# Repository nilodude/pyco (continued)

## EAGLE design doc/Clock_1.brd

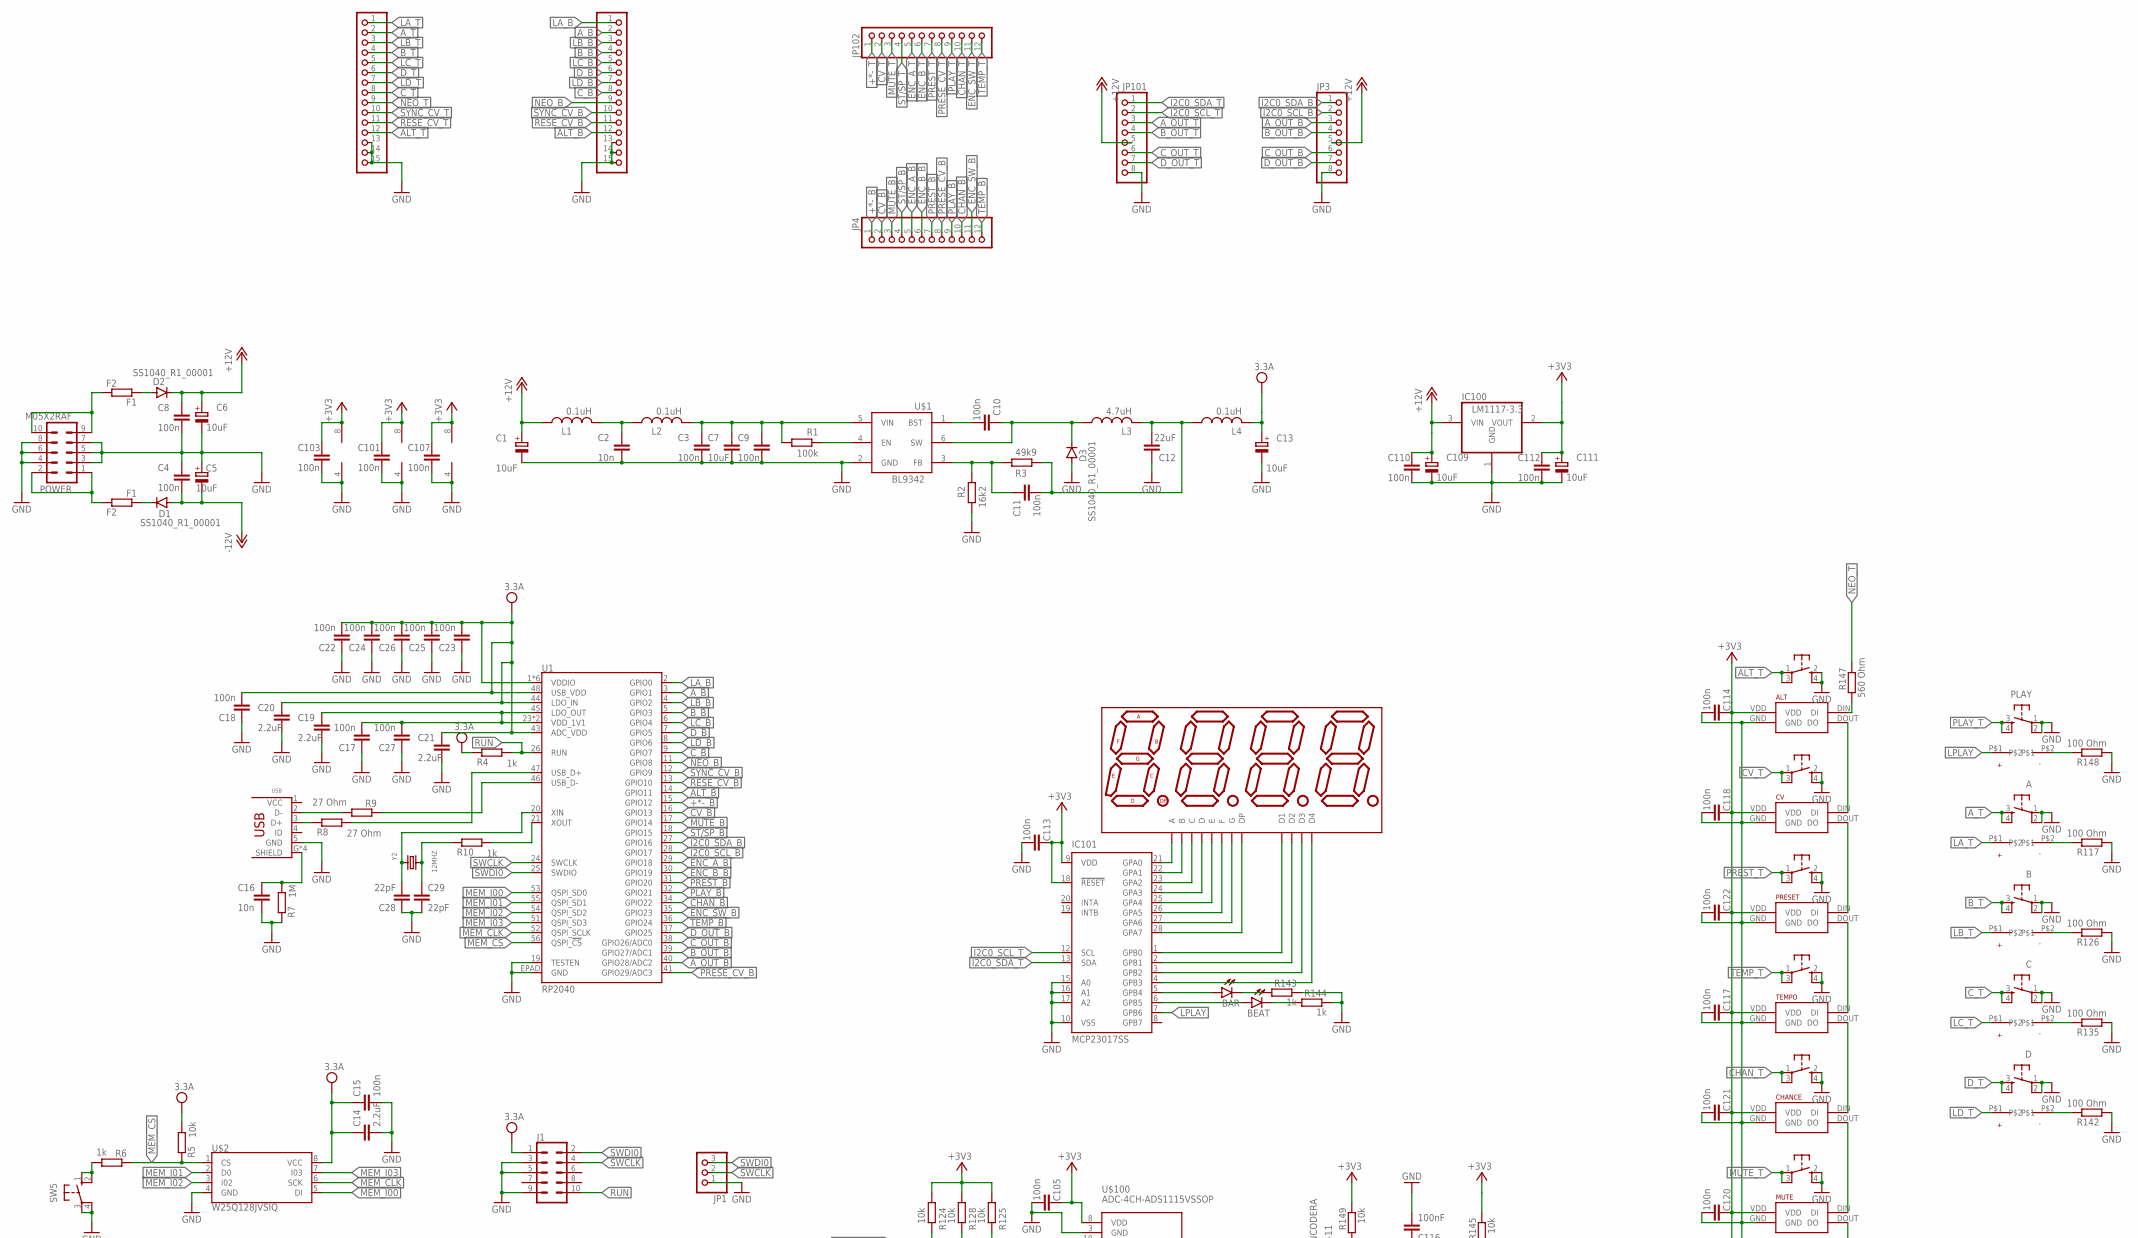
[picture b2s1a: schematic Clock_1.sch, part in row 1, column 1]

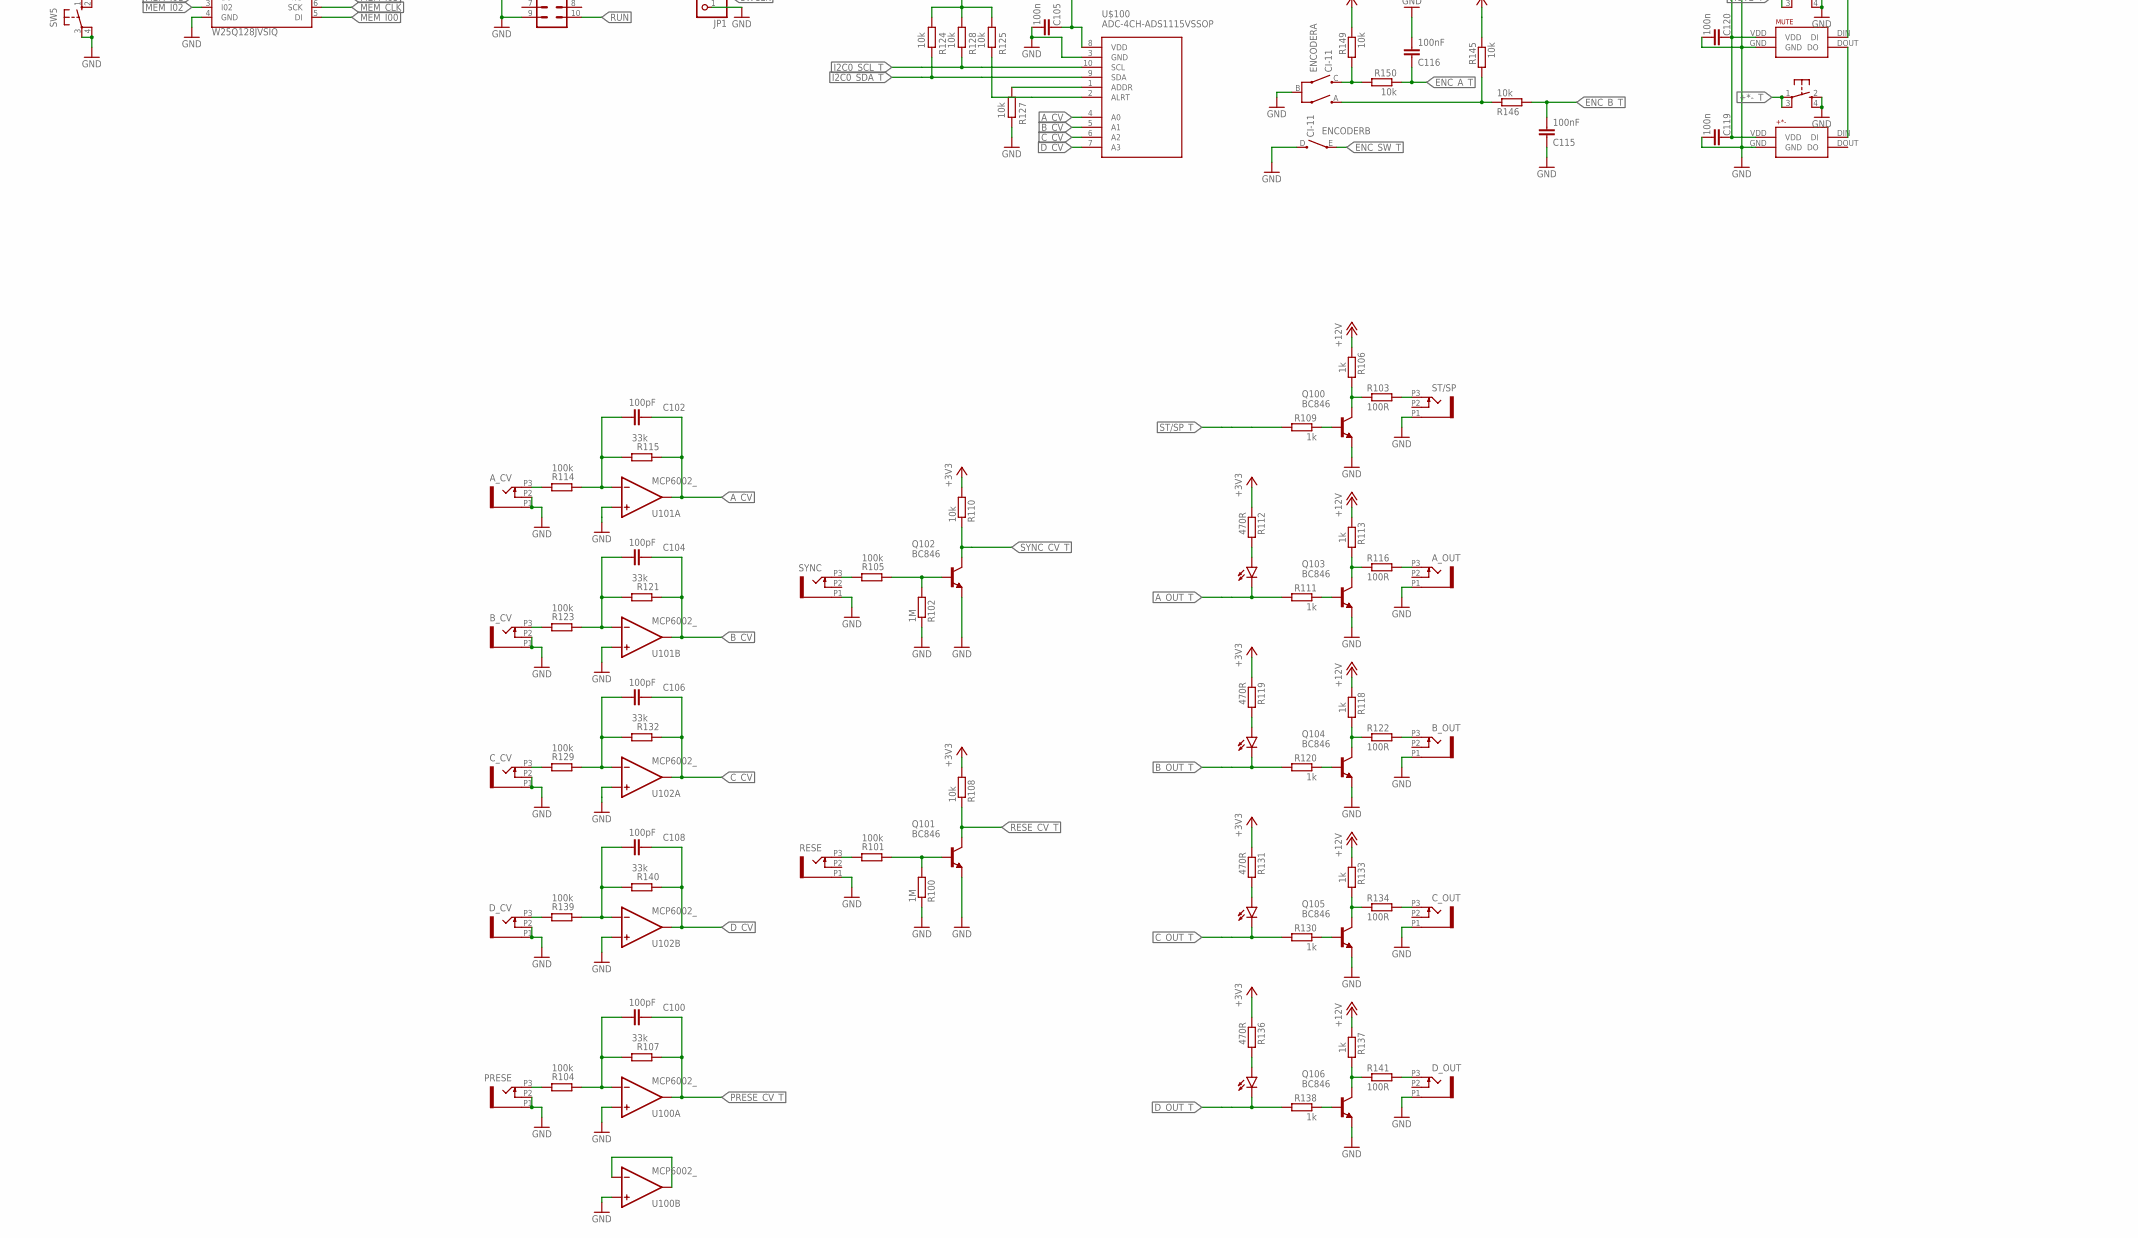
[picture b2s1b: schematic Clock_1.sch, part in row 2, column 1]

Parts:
+*-: BUTTON_NEOPIXELBUTTON_PIXEL_ç; BUTTON_PIXEL_ç
A: DTS-6_LEDTME; TMEBUTTON
ALT: BUTTON_NEOPIXELBUTTON_PIXEL_ç; BUTTON_PIXEL_ç
A_CV: OG-PJ301_PJ301_THONKICONNNOHOLER; NOHOLER_GND_SHORT_PADMINI_GND
A_OUT: OG-PJ301_PJ301_THONKICONNNOHOLER; NOHOLER_GND_SHORT_PADMINI_GND
B: DTS-6_LEDTME; TMEBUTTON
BAR: 2 MM LED; LED3MM
BEAT: 2 MM LED; LED3MM
B_CV: OG-PJ301_PJ301_THONKICONNNOHOLER; NOHOLER_GND_SHORT_PADMINI_GND
B_OUT: OG-PJ301_PJ301_THONKICONNNOHOLER; NOHOLER_GND_SHORT_PADMINI_GND
C: DTS-6_LEDTME; TMEBUTTON
C1, C5, C6, C13, C109, C111: 10uF; PANASONIC_B
C2, C16: 10n; C0603
C3, C4, C8, C9, C10, C11, C15, C17, C18, C22, C23, C24, C25, C26, C27, C101, C103, C105, C107, C110, C112, C113, C114, C117, C118, C119, C120, C121, C122: 100n; C0603
C7: 10uF; C0603
C12: 22uF; C0603
C14, C19, C20, C21: 2.2uF; C0603
C28, C29: 22pF; C0603
C100, C102, C104, C106, C108: 100pF; C0603
C115, C116: 100nF; C0603
CHANCE: BUTTON_NEOPIXELBUTTON_PIXEL_ç; BUTTON_PIXEL_ç
CV: BUTTON_NEOPIXELBUTTON_PIXEL_ç; BUTTON_PIXEL_ç
C_CV: OG-PJ301_PJ301_THONKICONNNOHOLER; NOHOLER_GND_SHORT_PADMINI_GND
C_OUT: OG-PJ301_PJ301_THONKICONNNOHOLER; NOHOLER_GND_SHORT_PADMINI_GND
D: DTS-6_LEDTME; TMEBUTTON
D1, D2, D3: SS1040_R1_00001; SOD123
D_CV: OG-PJ301_PJ301_THONKICONNNOHOLER; NOHOLER_GND_SHORT_PADMINI_GND
D_OUT: OG-PJ301_PJ301_THONKICONNNOHOLER; NOHOLER_GND_SHORT_PADMINI_GND
ENCODER: CI-11
F1: F2; R0603
F2: F1; R0603
IC100: LM1117-3.3; SOT223
IC101: MCP23017SS; SSOP28
J1: CONN_05X2RA; 2X5-RA
JP1: PINHD-1X31X3*; 1X3*
JP2, JP100: PINHD-1X151X15ç; 1X15ç
JP3, JP101: PINHD-1X81X8ç; 1X8ç
JP4, JP102: PINHD-1X12Ç; 1X12Ç
L1, L2, L4: 0.1uH; L3225P
L3: 4.7uH; L3225P
LED_A_OUT: 2 MM LED; LED3MM
LED_B_OUT: 2 MM LED; LED3MM
LED_C_OUT: 2 MM LED; LED3MM
LED_D_OUT: 2 MM LED; LED3MM
LFD36BUE-101B: 7-SEGMENT-4DIGIT-20MM; 7-SEGMENT-4DIGIT-30MM
MUTE: BUTTON_NEOPIXELBUTTON_PIXEL_ç; BUTTON_PIXEL_ç
PLAY: DTS-6_LED; TIMEBUTTON_HOLES_LEDS
POWER: M05X2RAF; 2X5-POWER_ACODADO
PRESE: OG-PJ301_PJ301_THONKICONNNOHOLER; NOHOLER_GND_SHORT_PADMINI_GND
PRESET: BUTTON_NEOPIXELBUTTON_PIXEL_ç; BUTTON_PIXEL_ç
Q100, Q101, Q102, Q103, Q104, Q105, Q106: BC846; SOT23
R1, R101, R104, R105, R114, R123, R129, R139: 100k; R0603
R2: 16k2; R0603
R3: 49k9; R0603
R4, R6, R10, R106, R109, R111, R113, R118, R120, R130, R133, R137, R138, R143, R144: 1k; R0603
R5, R108, R110, R124, R125, R127, R128, R145, R146, R149, R150: 10k; R0603
R7, R100, R102: 1M; R0603
R8, R9: 27 Ohm; R0603
R103, R116, R122, R134, R141: 100R; R0603
R107, R115, R121, R132, R140: 33k; R0603
R112, R119, R131, R136: 470R; R0603
R117, R126, R135, R142, R148: 100 Ohm; R0603
R147: 560 Ohm; R0603
RESE: OG-PJ301_PJ301_THONKICONNNOHOLER; NOHOLER_GND_SHORT_PADMINI_GND
ST/SP: OG-PJ301_PJ301_THONKICONNNOHOLER; NOHOLER_GND_SHORT_PADMINI_GND
SW5: 10-XX; B3F-10XX
SYNC: OG-PJ301_PJ301_THONKICONNNOHOLER; NOHOLER_GND_SHORT_PADMINI_GND
TEMPO: BUTTON_NEOPIXELBUTTON_PIXEL_ç; BUTTON_PIXEL_ç
U1: RP2040; QFN-56
U100, U101, U102: MCP6002_; SO08
U$1: BL9342; SOT23-6
U$2: W25Q128JVSIQ; SOIC-8
U$100: ADC-4CH-ADS1115VSSOP; ADC-4CH-ADS1115-VSSOP
USB: USB_HRS_ZX62-B-5PA(11)MICRO.B; HRS_ZX62RD-AB-5P8
Y2: 12MHZ; CRYSTAL_2.5X2

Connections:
+3V3: +*-.VDD, ALT.VDD, C101.1, C103.1, C105.1, C107.1, C111.+, C112.1, C113.1, C114.1, C117.1, C118.1, C119.1, C120.1, C121.1, C122.1, CHANCE.VDD, CV.VDD, IC100.2 (VOUT), IC101.9 (VDD), IC101.18 (!RESET), MUTE.VDD, PRESET.VDD, R108.2, R110.2, R112.1, R119.1, R124.1, R125.1, R128.1, R131.1, R136.1, R145.1, R149.1, TEMPO.VDD, U100.8 (V+), U101.8 (V+), U102.8 (V+), U$100.8 (VDD)
+12V: C1.+, C6.+, C8.1, C109.+, C110.1, D2.C, IC100.3 (VIN), JP3.5, JP101.5, L1.1, R106.1, R113.1, R118.1, R133.1, R137.1
+*-_B: JP4.1, U1.15 (GPIO12)
+*-_T: +*-.1, +*-.3, JP102.1
-12V: C4.2, C5.-, D1.A
ALT_B: JP2.12, U1.14 (GPIO11)
ALT_T: ALT.1, ALT.3, JP100.12
A_B: JP2.2, U1.3 (GPIO1)
A_CV: C102.2, R115.1, U101.1 (OUT), U$100.4 (A0)
A_OUT_B: JP3.3, U1.40 (GPIO28/ADC2)
A_OUT_T: JP101.3, LED_A_OUT.K (C), R111.2
A_T: A.3, A.4, JP100.2
B_B: JP2.4, U1.5 (GPIO3)
B_CV: C104.2, R121.1, U101.7 (OUT), U$100.5 (A1)
B_OUT_B: JP3.4, U1.39 (GPIO27/ADC1)
B_OUT_T: JP101.4, LED_B_OUT.K (C), R120.2
B_T: B.3, B.4, JP100.4
CHAN_B: JP4.10, U1.34 (GPIO22)
CHAN_T: CHANCE.1, CHANCE.3, JP102.10
CV_B: JP4.2, U1.16 (GPIO13)
CV_T: CV.1, CV.3, JP102.2
C_B: JP2.8, U1.9 (GPIO7)
C_CV: C106.2, R132.1, U102.1 (OUT), U$100.6 (A2)
C_OUT_B: JP3.6, U1.38 (GPIO26/ADC0)
C_OUT_T: JP101.6, LED_C_OUT.K (C), R130.2
C_T: C.3, C.4, JP100.8
D_B: JP2.6, U1.7 (GPIO5)
D_CV: C108.2, R140.1, U102.7 (OUT), U$100.7 (A3)
D_OUT_B: JP3.7, U1.37 (GPIO25)
D_OUT_T: JP101.7, LED_D_OUT.K (C), R138.2
D_T: D.3, D.4, JP100.6
ENC_A_B: JP4.5, U1.29 (GPIO18)
ENC_A_T: C116.1, JP102.5, R150.1
ENC_B_B: JP4.6, U1.30 (GPIO19)
ENC_B_T: C115.2, JP102.6, R146.2
ENC_SW_B: JP4.11, U1.35 (GPIO23)
ENC_SW_T: ENCODER.E, JP102.11
GND: +*-.2, +*-.4, +*-.GND, A.1, A.2, ALT.2, ALT.4, ALT.GND, A_CV.P1 (1), A_CV.P2 (2), A_OUT.P1 (1), B.1, B.2, B_CV.P1 (1), B_CV.P2 (2), B_OUT.P1 (1), C.1, C.2, C1.-, C2.2, C3.2, C4.1, C5.+, C6.-, C7.2, C8.2, C9.2, C12.1, C13.-, C14.2, C15.2, C16.2, C17.1, C18.1, C19.2, C20.2, C21.2, C22.1, C23.1, C24.1, C25.1, C26.1, C27.1, C28.1, C29.2, C101.2, C103.2, C105.2, C107.2, C109.-, C110.2, C111.-, C112.2, C113.2, C114.2, C115.1, C116.2, C117.2, C118.2, C119.2, C120.2, C121.2, C122.2, CHANCE.2, CHANCE.4, CHANCE.GND, CV.2, CV.4, CV.GND, C_CV.P1 (1), C_CV.P2 (2), C_OUT.P1 (1), D.1, D.2, D3.A, D_CV.P1 (1), D_CV.P2 (2), D_OUT.P1 (1), ENCODER.B (C), ENCODER.D, IC100.1 (GND), IC101.10 (VSS), IC101.15 (A0), IC101.16 (A1), IC101.17 (A2), J1.3, J1.5, J1.9, JP1.1, JP2.13, JP2.14, JP2.15, JP3.8, JP100.13, JP100.14, JP100.15, JP101.8, MUTE.2, MUTE.4, MUTE.GND, PLAY.1, PLAY.2, POWER.3, POWER.4, POWER.5, POWER.6, POWER.7, POWER.8, PRESE.P1 (1), PRESE.P2 (2), PRESET.2, PRESET.4, PRESET.GND, Q100.2 (E), Q101.2 (E), Q102.2 (E), Q103.2 (E), Q104.2 (E), Q105.2 (E), Q106.2 (E), R2.1, R7.1, R100.1, R102.1, R117.2, R126.2, R127.2, R135.2, R142.2, R143.1, R144.1, R148.2, RESE.P1 (1), ST/SP.P1 (1), SW5.3, SW5.4 (P1), SYNC.P1 (1), TEMPO.2, TEMPO.4, TEMPO.GND, U1.19 (TESTEN), U1.EPAD (GND), U100.3 (+IN), U100.4 (V-), U100.5 (+IN), U101.3 (+IN), U101.4 (V-), U101.5 (+IN), U102.3 (+IN), U102.4 (V-), U102.5 (+IN), U$1.2 (GND), U$2.4 (GND), U$100.3 (GND), USB.5 (GND)
I2C0_SCL_B: JP3.2, U1.28 (GPIO17)
I2C0_SCL_T: IC101.12 (SCL), JP101.2, R128.2, U$100.10 (SCL)
I2C0_SDA_B: JP3.1, U1.27 (GPIO16)
I2C0_SDA_T: IC101.13 (SDA), JP101.1, R124.2, U$100.9 (SDA)
LA_B: JP2.1, U1.2 (GPIO0)
LA_T: A.P$1, JP100.1
LB_B: JP2.3, U1.4 (GPIO2)
LB_T: B.P$1, JP100.3
LC_B: JP2.5, U1.6 (GPIO4)
LC_T: C.P$1, JP100.5
LD_B: JP2.7, U1.8 (GPIO6)
LD_T: D.P$1, JP100.7
LPLAY: IC101.7 (GPB6), PLAY.P$1
MEM_CLK: U1.52 (QSPI_SCLK), U$2.6 (SCK)
MEM_CS: R5.1, R6.1, U1.56 (QSPI_!CS!), U$2.1 (CS)
MEM_I00: U1.53 (QSPI_SD0), U$2.5 (DI)
MEM_I01: U1.55 (QSPI_SD1), U$2.2 (D0)
MEM_I02: U1.54 (QSPI_SD2), U$2.3 (I02)
MEM_I03: U1.51 (QSPI_SD3), U$2.7 (I03)
MUTE_B: JP4.3, U1.17 (GPIO14)
MUTE_T: JP102.3, MUTE.1, MUTE.3
unnamed: R10.2, U1.21 (XOUT)
unnamed: C28.2, U1.20 (XIN), Y2.3 (2)
unnamed: C29.1, R10.1, Y2.1
unnamed: R1.2, U$1.4 (EN)
unnamed: C3.1, C7.1, C9.1, L2.2, R1.1, U$1.5 (VIN)
unnamed: C2.1, L1.2, L2.1
unnamed: C10.2, U$1.1 (BST)
unnamed: C10.1, D3.C, L3.1, U$1.6 (SW)
unnamed: C11.1, R2.2, R3.2, U$1.3 (FB)
unnamed: C11.2, C12.2, L3.2, L4.1, R3.1
unnamed: IC101.21 (GPA0), LFD36BUE-101B.11 (A)
unnamed: R8.2, U1.47 (USB_D+)
unnamed: BAR.A, IC101.5 (GPB4)
unnamed: R9.1, U1.46 (USB_D-)
unnamed: C16.1, R7.2, USB.G (SHIELD), USB.G2 (SHIELD), USB.G3 (SHIELD), USB.G4 (SHIELD)
unnamed: IC101.22 (GPA1), LFD36BUE-101B.7 (B)
unnamed: R6.2, SW5.1 (S), SW5.2 (S1)
unnamed: IC101.23 (GPA2), LFD36BUE-101B.4 (C)
unnamed: IC101.24 (GPA3), LFD36BUE-101B.2 (D)
unnamed: IC101.25 (GPA4), LFD36BUE-101B.1 (E)
unnamed: IC101.26 (GPA5), LFD36BUE-101B.10 (F)
unnamed: IC101.27 (GPA6), LFD36BUE-101B.5 (G)
unnamed: IC101.28 (GPA7), LFD36BUE-101B.3 (DP)
unnamed: IC101.1 (GPB0), LFD36BUE-101B.12 (D1)
unnamed: IC101.2 (GPB1), LFD36BUE-101B.9 (D2)
unnamed: IC101.3 (GPB2), LFD36BUE-101B.8 (D3)
unnamed: IC101.4 (GPB3), LFD36BUE-101B.6 (D4)
unnamed: C102.1, R114.1, R115.2, U101.2 (-IN)
unnamed: ALT.DIN (DI), R147.2
unnamed: ALT.DOUT (DO), CV.DIN (DI)
unnamed: CV.DOUT (DO), PRESET.DIN (DI)
unnamed: PRESET.DOUT (DO), TEMPO.DIN (DI)
unnamed: CHANCE.DIN (DI), TEMPO.DOUT (DO)
unnamed: CHANCE.DOUT (DO), MUTE.DIN (DI)
unnamed: +*-.DIN (DI), MUTE.DOUT (DO)
unnamed: U100.6 (-IN), U100.7 (OUT)
unnamed: C104.1, R121.2, R123.1, U101.6 (-IN)
unnamed: C106.1, R129.1, R132.2, U102.2 (-IN)
unnamed: C108.1, R139.1, R140.2, U102.6 (-IN)
unnamed: PLAY.P$2, R148.1
unnamed: A.P$2, R117.1
unnamed: B.P$2, R126.1
unnamed: F2.2, POWER.9, POWER.10
unnamed: D2.A, F2.1
unnamed: F1.2, POWER.1, POWER.2
unnamed: D1.C, F1.1
unnamed: C.P$2, R135.1
unnamed: D.P$2, R142.1
unnamed: A_OUT.P3 (3), R116.2
unnamed: B_OUT.P3 (3), R122.2
unnamed: Q102.1 (B), R102.2, R105.1
unnamed: C_OUT.P3 (3), R134.2
unnamed: Q101.1 (B), R100.2, R101.1
unnamed: D_OUT.P3 (3), R141.2
unnamed: Q100.1 (B), R109.1
unnamed: A_CV.P3 (3), R114.2
unnamed: B_CV.P3 (3), R123.2
unnamed: C_CV.P3 (3), R129.2
unnamed: D_CV.P3 (3), R139.2
unnamed: R103.2, ST/SP.P3 (3)
unnamed: Q100.3 (C), R103.1, R106.2
unnamed: R105.2, SYNC.P3 (3)
unnamed: PRESE.P3 (3), R104.2
unnamed: R101.2, RESE.P3 (3)
unnamed: ENCODER.A, R145.2, R146.1
unnamed: ENCODER.C (B), R149.2, R150.2
unnamed: BAR.K (C), R143.2
unnamed: BEAT.A, IC101.6 (GPB5)
unnamed: BEAT.K (C), R144.2
unnamed: R8.1, USB.3 (D+)
unnamed: C100.1, R104.1, R107.2, U100.2 (-IN)
unnamed: R127.1, U$100.1 (ADDR)
unnamed: R125.2, U$100.2 (ALRT)
unnamed: Q103.1 (B), R111.1
unnamed: Q103.3 (C), R113.2, R116.1
unnamed: LED_A_OUT.A, R112.2
unnamed: R9.2, USB.2 (D-)
unnamed: Q104.1 (B), R120.1
unnamed: Q104.3 (C), R118.2, R122.1
unnamed: LED_B_OUT.A, R119.2
unnamed: Q105.1 (B), R130.1
unnamed: Q105.3 (C), R133.2, R134.1
unnamed: LED_C_OUT.A, R131.2
unnamed: C17.2, C19.1, C27.2, U1.23 (VDD_1V1), U1.45 (LDO_OUT), U1.50 (VDD_1V1)
unnamed: Q106.1 (B), R138.1
unnamed: Q106.3 (C), R137.2, R141.1
unnamed: LED_D_OUT.A, R136.2
NEO_B: JP2.9, U1.11 (GPIO8)
NEO_T: JP100.9, R147.1
PLAY_B: JP4.9, U1.32 (GPIO21)
PLAY_T: JP102.9, PLAY.3, PLAY.4
PRESE_CV_B: JP4.8, U1.41 (GPIO29/ADC3)
PRESE_CV_T: C100.2, JP102.8, R107.1, U100.1 (OUT)
PREST_B: JP4.7, U1.31 (GPIO20)
PREST_T: JP102.7, PRESET.1, PRESET.3
RESE_CV_B: JP2.11, U1.13 (GPIO10)
RESE_CV_T: JP100.11, Q101.3 (C), R108.1
RUN: J1.10, R4.2, U1.26 (RUN)
ST/SP_B: JP4.4, U1.18 (GPIO15)
ST/SP_T: JP102.4, R109.2
SWCLK: J1.4, JP1.2, U1.24 (SWCLK)
SWDI0: J1.2, JP1.3, U1.25 (SWDIO)
SYNC_CV_B: JP2.10, U1.12 (GPIO9)
SYNC_CV_T: JP100.10, Q102.3 (C), R110.1
TEMP_B: JP4.12, U1.36 (GPIO24)
TEMP_T: JP102.12, TEMPO.1, TEMPO.3
VCC: C13.+, C14.1, C15.1, C18.2, C20.1, C21.1, C22.2, C23.2, C24.2, C25.2, C26.2, J1.1, L4.2, R4.1, R5.2, U1.1 (VDDIO), U1.10 (VDDIO), U1.22 (VDDIO), U1.33 (VDDIO), U1.42 (VDDIO), U1.43 (ADC_VDD), U1.44 (LDO_IN), U1.48 (USB_VDD), U1.49 (VDDIO), U$2.8 (VCC)

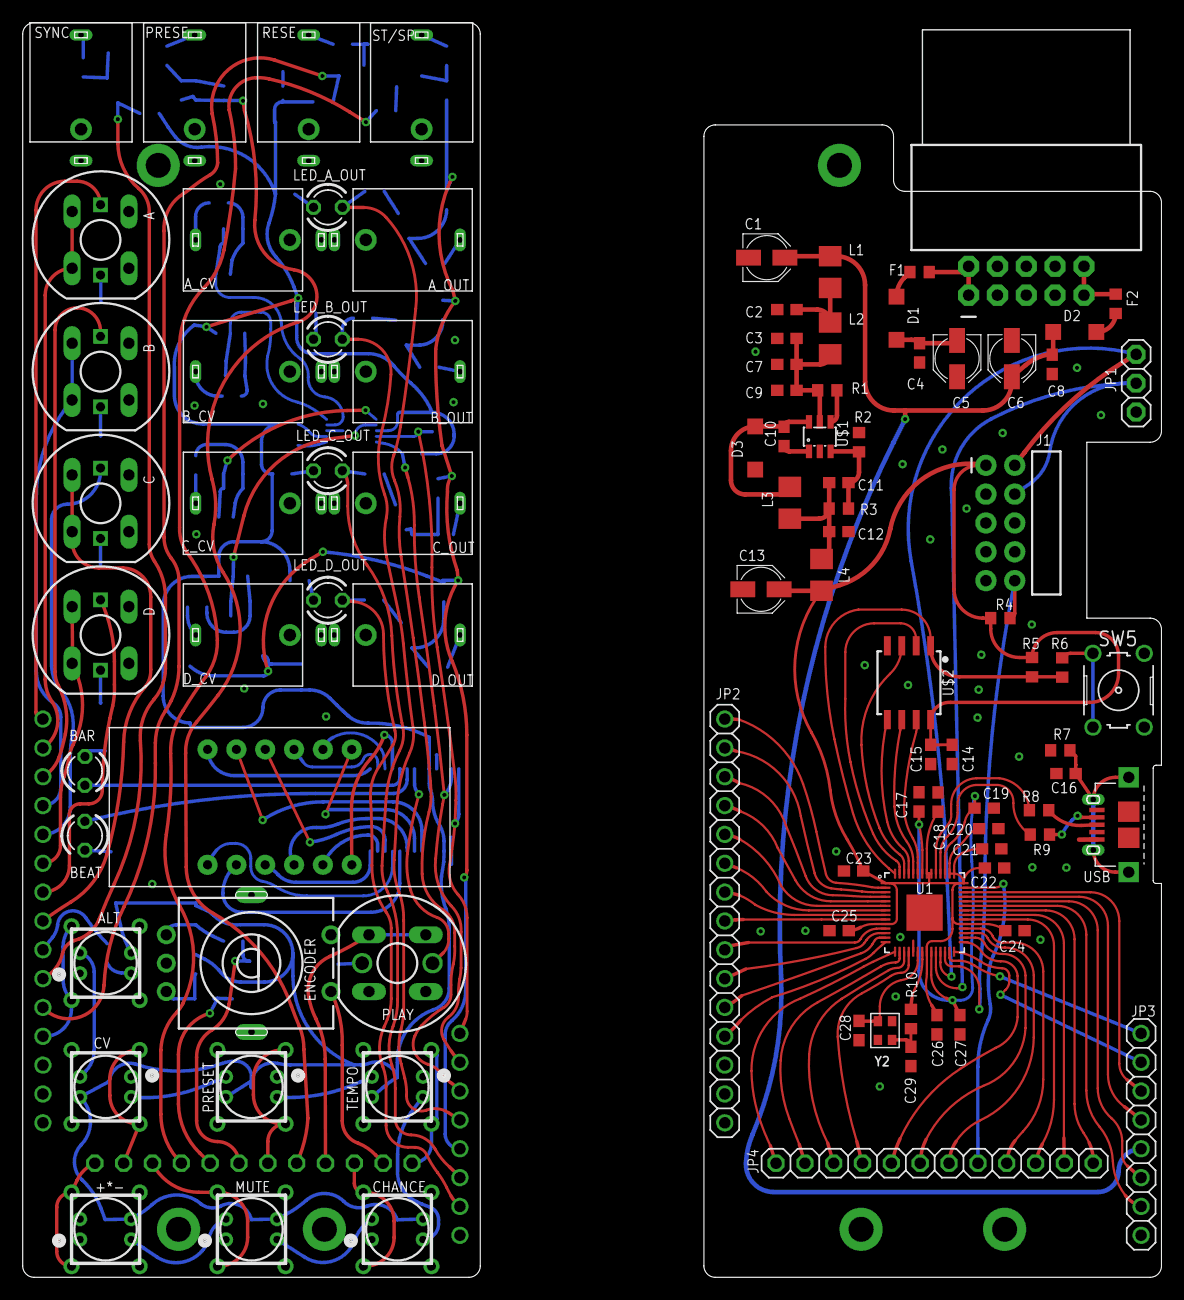
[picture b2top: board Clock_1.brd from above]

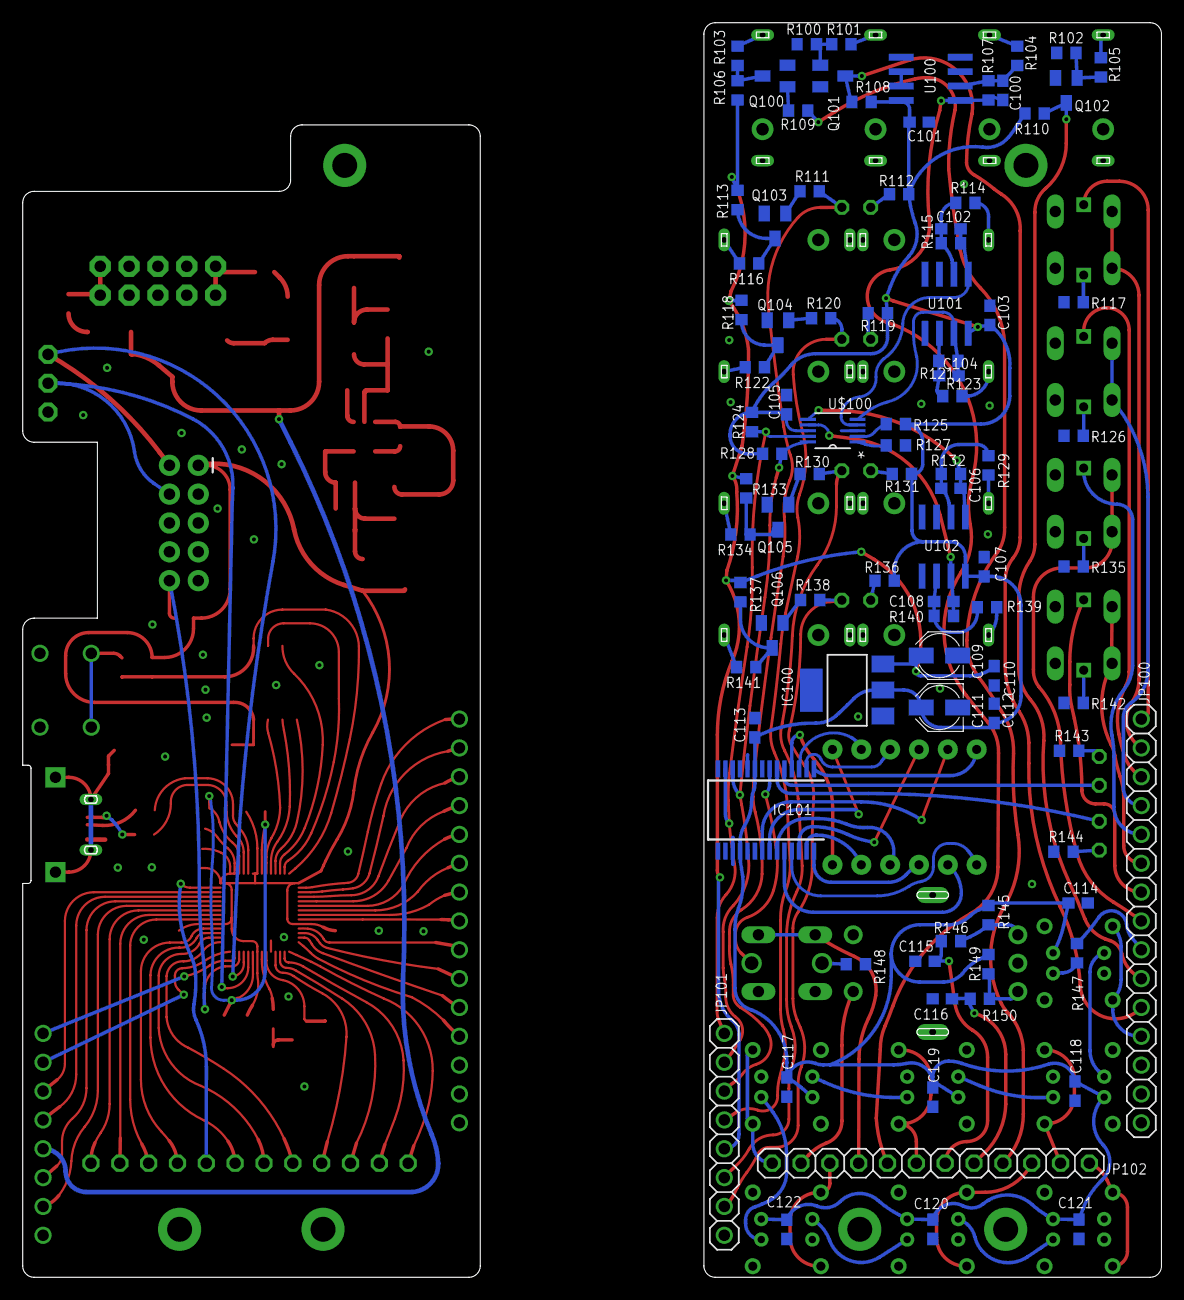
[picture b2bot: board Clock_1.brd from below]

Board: 2 copper layers, 100.3 x 110.5 mm, 182 parts (90 on the bottom side), 166 nets.

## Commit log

2024-02-14 files. connection to mcp23017 ok
2024-02-14 sending info to 7segments OK
2024-02-14 still missmatching portA & portB connections
2024-02-14 portB "works" with connected protoboard
2024-02-14 software OK, bad connections
2024-02-14 mapped some numbers
2024-02-14 reading encoder & sending data to 7 segment
2024-02-15 switching off each display before lighting up next one
2024-02-15 handle counter overflow
2024-02-15 finetuning sleep between displays & ADC i2c1 OK
2024-02-15 adc works as expected
2024-02-15 refactored, adc showing on screen
2024-02-16 1 neopixel OK. need to test >1
2024-02-16 redBtn OK
2024-02-16 about to optimize display by reverting string
2024-02-16 optimized display loop
2024-02-16 adc same bus i2c0 as mux
2024-02-24 drauio
2024-02-25 import errors but seems OK
2024-02-25 refactoring buttons to class
2024-02-25 encoder class
2024-02-25 remove comments
2024-03-21 neopixel matrix 99% plug n play
2024-03-21 notes about 16x16 leds
2024-04-09 check if i2c connected. setup OK. need to solder components
2024-04-10 red buttons input OK. some leds not OK
2024-04-10 i2c OK
2024-04-10 about to fix display
2024-04-11 need to update screenshots. need to handle PORTB
2024-04-11 pixelbuttons assigned.
2024-04-11 encoder OK.
2024-04-11 numbers & display access dict instead of array
2024-04-11 buttons OK. pending pixels
2024-04-11 neopixel OK. outLed, beatLed, barLed OK
2024-04-11 ADC pending
2024-04-11 some cleanup. need to rethink display & ADC config
2024-04-25 added buttons
2024-04-25 need to check BEAT led
2024-04-25 display not consistent
2024-04-25 fix 5
2024-04-25 need to refactor selectDisplay
2024-04-25 hardware input voltage cant be negative
2024-04-25 need to rewrite number2display
2024-04-25 about to fix show display
2024-04-25 need to fix adc1, adc2, adc3
2024-04-25 need to fix adc inputs
2024-04-30 digital inputs OK
2024-04-30 start/stop OK
2024-04-30 need to handle multiple adc i2c inputs
2024-04-30 new ADC library works OK with 4 inputs
2024-04-30 need to handle correctly analog inputs as digital
2024-05-01 testing show display on interrupt
2024-05-01 fixed zero padding when display
2024-05-01 display still blocking loop. need to rethink
2024-05-01 still not refreshing correctly
2024-05-01 seem to show each input hitting redbutton
2024-05-01 switch CV input display with redbutton
2024-05-02 slight refactor
2024-05-02 need to define timestep & manual high/low states for outputs
2024-05-02 notes
2024-05-03 PWM rocking the avenue
2024-05-03 freq modifier works like a charm
2024-05-03 pwm too fast
2024-05-03 going to need custom timing
2024-05-03 about to implement manual clock timing
2024-05-03 need to implement own version
2024-05-06 fixed encoder
2024-05-07 trying to toggle pin through PIO
2025-06-21 starting to remap pins
2025-06-22 Auto stash before merge of "develop" and "origin/develop"
2025-08-09 docs & important notes
2025-08-09 need to remap I2C pins
2025-08-09 still remapping pins
2025-08-09 pin > 30 not recognized
2025-08-09 re-uniting with my own code
    need to clarify pinout
